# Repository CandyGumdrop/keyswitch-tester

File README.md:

Cherry-Compatible Keyswitch Tester
==================================

This is a simple keyswitch tester PCB for Cherry-compatible mechanical keyboard
switches.  It holds four keyswitches using Kailh's hotswap switch sockets and
has an LED wired to each switch, providing a quick and simple way to test the
actuation point of various switches.  This board is powered either by a
MicroUSB connector, or optionally instead via a 2 x 0.1" header connected to a
5 V power supply.

Most of this board can easily be assembled by hand, except for the MicroUSB
connector which is a bit more tricky, so if soldering this by hand, you may
prefer to use the header pins instead.

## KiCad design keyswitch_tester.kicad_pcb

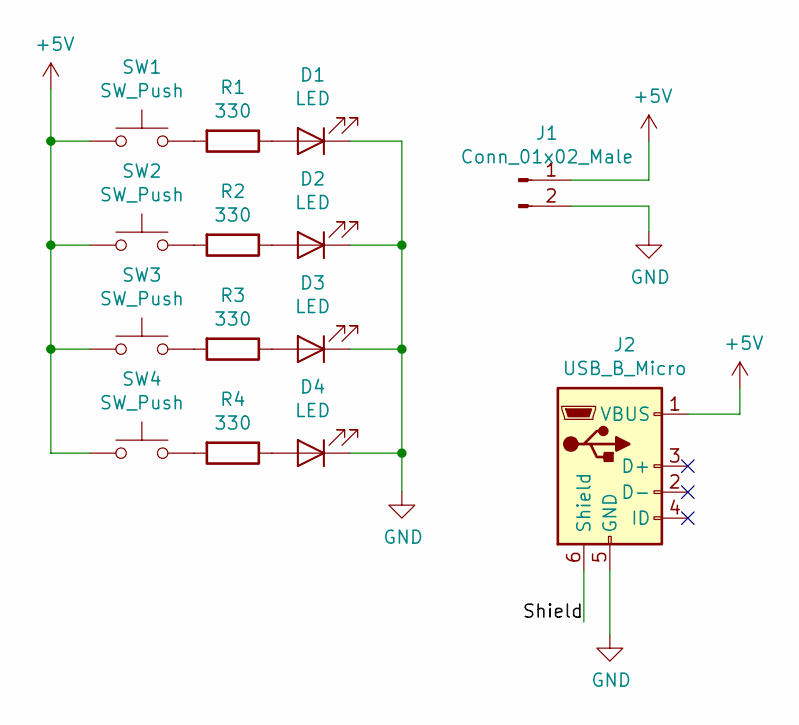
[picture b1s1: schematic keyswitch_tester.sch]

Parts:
D1, D2, D3, D4: LED; LED_D5.0mm
J1: Conn_01x02_Male; PinHeader_1x02_P2.54mm_Vertical
J2: USB_B_Micro; USB_Micro-B_Wuerth_629105150521
R1, R2, R3, R4: 330; R_Axial_DIN0207_L6.3mm_D2.5mm_P10.16mm_Horizontal
SW1, SW2, SW3, SW4: SW_Push; Kailh_socket

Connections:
+5V: J1.1, J2.1 (VBUS), SW1.1, SW2.1, SW3.1, SW4.1
/Shield: J2.6 (Shield)
GND: D1.1 (K), D2.1 (K), D3.1 (K), D4.1 (K), J1.2, J2.5 (GND)
unnamed: D1.2 (A), R1.1
unnamed: D2.2 (A), R2.1
unnamed: D3.2 (A), R3.1
unnamed: D4.2 (A), R4.1
unnamed: R1.2, SW1.2
unnamed: R2.2, SW2.2
unnamed: R3.2, SW3.2
unnamed: R4.2, SW4.2

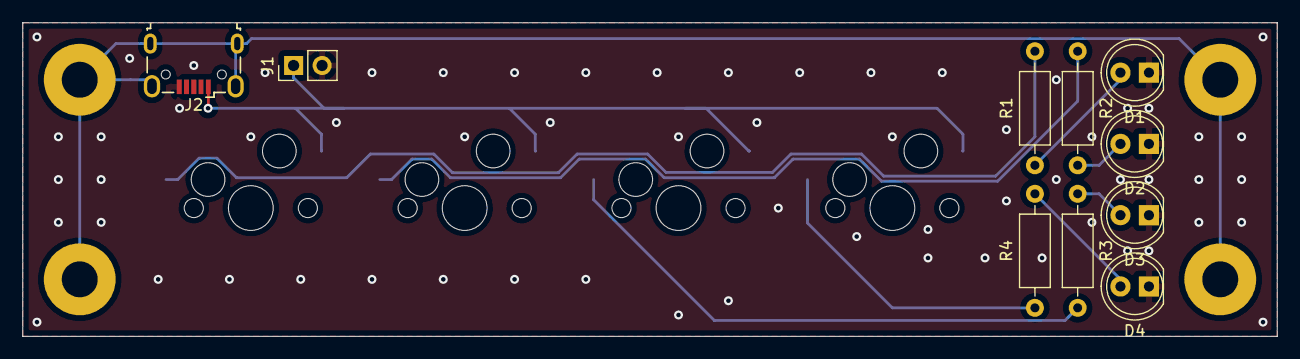
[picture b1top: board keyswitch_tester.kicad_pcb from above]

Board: 2 copper layers, 111.8 x 27.9 mm, 14 parts (0 on the bottom side), 10 nets.

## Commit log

2019-05-14 Add COPYING
2019-05-14 Add drawing + schematic images
